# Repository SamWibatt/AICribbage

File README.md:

# MIGRATING FROM GITHUB TO GITLAB AT https://gitlab.com/SamWibatt/aicribbage - please go to that repository (unless you're already there.)

# AICribbage
Learned models for cribbage playing: discard, next card in count.

No learned players have yet been constructed - computer player is random / first legal pick.

# Status

As of (7/27/20), early. Python prototype (pybbage) that is the framework for learned players is complete and its correctness wrt American Cribbage Congress rules verified through unit testing. It has a text interface for playing it. 

**C++ development has been split off into [cribbage_cpp](https://github.com/SamWibatt/cribbage_cpp), where pybbage's functionality has been duplicated and verified through unit testing**.

# objective

* More self-teaching, this is like a "semester project" for showing I can use modern AI methods.
* Construct models for two player game, see if can transfer to others
* First concept is if I have models to:
    * decide which cards to discard from hand that's dealt
        * both as dealer and non-dealer
    * decide which card to play next in count
* will sketch design in wiki

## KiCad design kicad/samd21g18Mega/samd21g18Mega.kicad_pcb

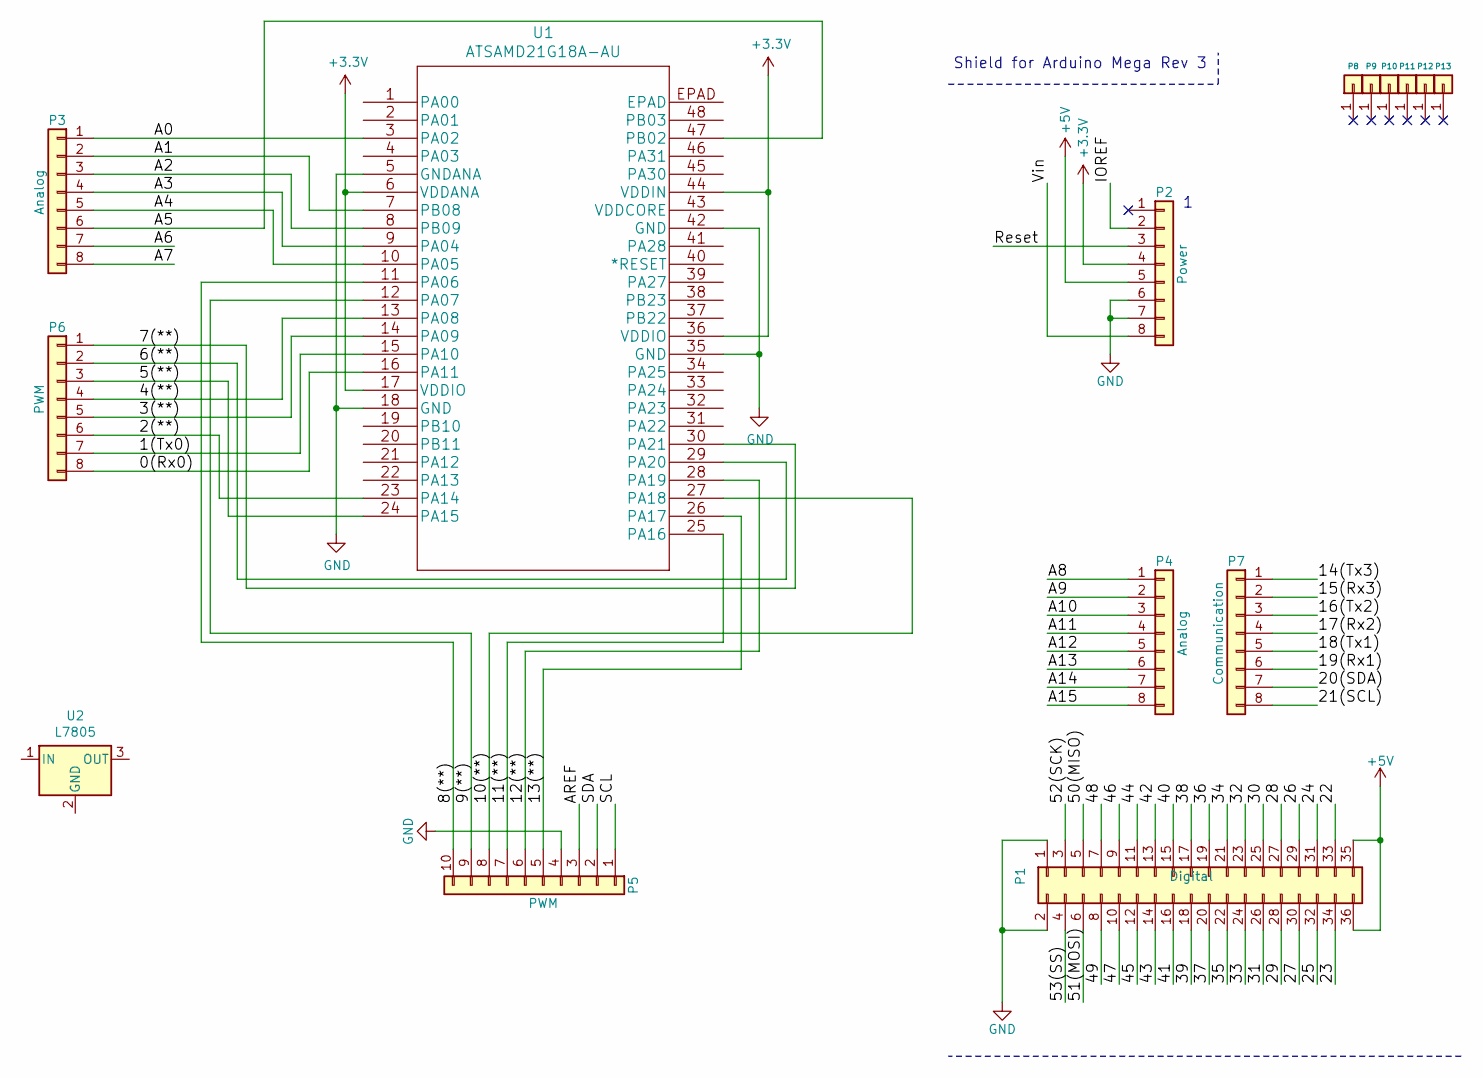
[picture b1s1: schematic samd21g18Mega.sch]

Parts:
P1: Digital; Socket_Strip_Arduino_2x18
P2: Power; Socket_Strip_Arduino_1x08
P3, P4: Analog; Socket_Strip_Arduino_1x08
P5: PWM; Socket_Strip_Arduino_1x10
P6: PWM; Socket_Strip_Arduino_1x08
P7: Communication; Socket_Strip_Arduino_1x08
P8, P9, P10, P11, P12, P13: CONN_01X01; Arduino_1pin
U1: ATSAMD21G18A-AU; DIP-48_W15.24mm
U2: L7805; TO-220-3_Horizontal_TabUp

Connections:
+3V3: P2.4, U1.6 (VDDANA), U1.17 (VDDIO), U1.36 (VDDIO), U1.44 (VDDIN)
+5V: P1.35, P1.36, P2.5
/0(Rx0): P6.8, U1.16 (PA11)
/1(Tx0): P6.7, U1.15 (PA10)
/2(**): P6.6, U1.23 (PA14)
/3(**): P6.5, U1.14 (PA09)
/4(**): P6.4, U1.13 (PA08)
/5(**): P6.3, U1.24 (PA15)
/6(**): P6.2, U1.29 (PA20)
/7(**): P6.1, U1.30 (PA21)
/8(**): P5.10, U1.11 (PA06)
/9(**): P5.9, U1.12 (PA07)
/10(**): P5.8, U1.27 (PA18)
/11(**): P5.7, U1.25 (PA16)
/12(**): P5.6, U1.28 (PA19)
/13(**): P5.5, U1.26 (PA17)
/14(Tx3): P7.1
/15(Rx3): P7.2
/16(Tx2): P7.3
/17(Rx2): P7.4
/18(Tx1): P7.5
/19(Rx1): P7.6
/20(SDA): P7.7
/21(SCL): P7.8
/22: P1.33
/23: P1.34
/24: P1.31
/25: P1.32
/26: P1.29
/27: P1.30
/28: P1.27
/29: P1.28
/30: P1.25
/31: P1.26
/32: P1.23
/33: P1.24
/34: P1.21
/35: P1.22
/36: P1.19
/37: P1.20
/38: P1.17
/39: P1.18
/40: P1.15
/41: P1.16
/42: P1.13
/43: P1.14
/44: P1.11
/45: P1.12
/46: P1.9
/47: P1.10
/48: P1.7
/49: P1.8
/50(MISO): P1.5
/51(MOSI): P1.6
/52(SCK): P1.3
/53(SS): P1.4
/A0: P3.1, U1.3 (PA02)
/A1: P3.2, U1.7 (PB08)
/A2: P3.3, U1.8 (PB09)
/A3: P3.4, U1.9 (PA04)
/A4: P3.5, U1.10 (PA05)
/A5: P3.6, U1.47 (PB02)
/A6: P3.7
/A7: P3.8
/A8: P4.1
/A9: P4.2
/A10: P4.3
/A11: P4.4
/A12: P4.5
/A13: P4.6
/A14: P4.7
/A15: P4.8
/AREF: P5.3
/IOREF: P2.2
/Reset: P2.3
/SCL: P5.1
/SDA: P5.2
/Vin: P2.8
GND: P1.1, P1.2, P2.6, P2.7, P5.4, U1.5 (GNDANA), U1.18 (GND), U1.35 (GND), U1.42 (GND)

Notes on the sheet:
Shield for Arduino Mega Rev 3

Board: 2 copper layers, 15 parts (0 on the bottom side), 23 nets, no tracks yet.

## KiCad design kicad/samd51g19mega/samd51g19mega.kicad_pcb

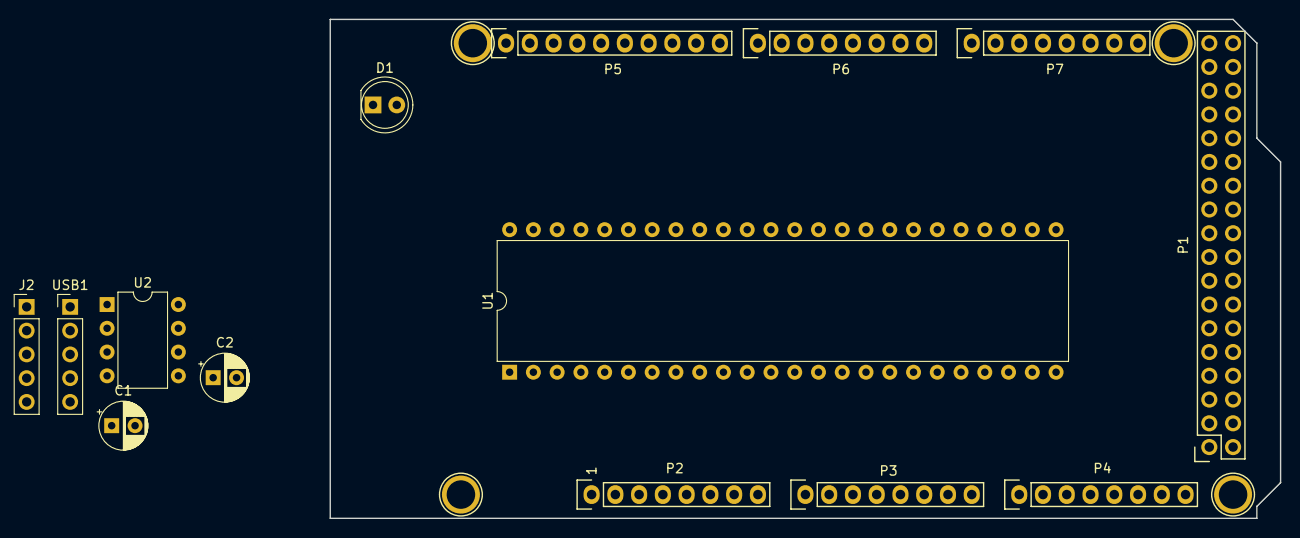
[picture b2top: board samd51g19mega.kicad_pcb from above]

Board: 2 copper layers, 101.6 x 53.3 mm, 18 parts (0 on the bottom side), 5 nets, no tracks yet.

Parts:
C1, C2: 10uF; CP_Radial_D5.0mm_P2.50mm
D1: LED; LED_D5.0mm
J2: Conn_01x05_Female; PinHeader_1x05_P2.54mm_Vertical
P1: Digital; Socket_Strip_Arduino_2x18
P2: Power; Socket_Strip_Arduino_1x08
P3, P4: Analog; Socket_Strip_Arduino_1x08
P5: PWM; Socket_Strip_Arduino_1x10
P6: PWM; Socket_Strip_Arduino_1x08
P7: Communication; Socket_Strip_Arduino_1x08
P8, P10, P11, P13: CONN_01X01; Arduino_1pin
U1: ATSAMD51G19A-MUT; DIP-48_W15.24mm
U2: W25Q64JVSSIQ; DIP-8_W7.62mm
USB1: USB_B_Micro; PinHeader_1x05_P2.54mm_Vertical

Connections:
+3V3: C2.1, P2.4
+5V: C1.1, J2.1, P1.35, P1.36, P2.5, USB1.1
GND: C1.2, C2.2, J2.5, P1.1, P1.2, P2.6, P2.7, P5.4, USB1.5
unnamed: J2.2, U1.33, USB1.2
unnamed: J2.3, U1.34, USB1.3

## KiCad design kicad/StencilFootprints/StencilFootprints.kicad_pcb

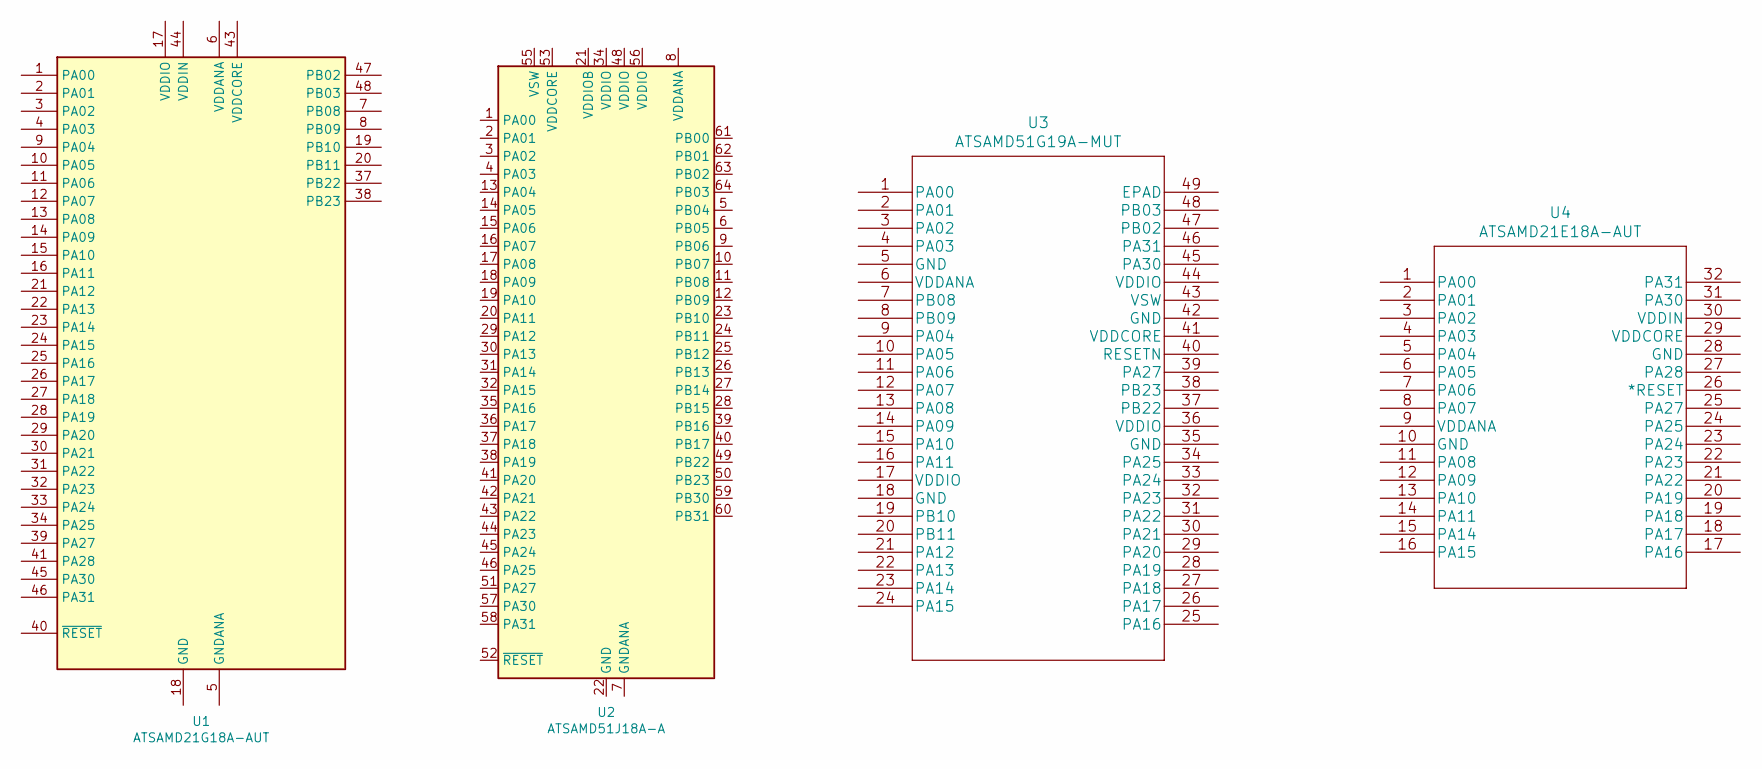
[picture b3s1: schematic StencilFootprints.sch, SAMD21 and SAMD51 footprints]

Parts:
U1: ATSAMD21G18A-AUT; TQFP-48_7x7mm_P0.5mm
U2: ATSAMD51J18A-A; TQFP-64_10x10mm_P0.5mm
U3: ATSAMD51G19A-MUT; QFN-48-1EP_7x7mm_P0.5mm_EP5.15x5.15mm
U4: ATSAMD21E18A-AUT; TQFP-32_7x7mm_P0.8mm

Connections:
unnamed: U1.17 (VDDIO), U1.36 (VDDIO)
unnamed: U1.18 (GND), U1.35 (GND), U1.42 (GND)
unnamed: U2.22 (GND), U2.33 (GND), U2.47 (GND), U2.54 (GND)

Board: 2 copper layers, 4 parts (0 on the bottom side), 3 nets, no tracks yet.

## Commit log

2020-03-08 set up pybbage project
2020-03-09 python prototype random
2020-03-12 shuffle and deal
2020-03-12 new shuffle and deal
2020-03-16 deal
2020-03-18 scoring 15s
2020-03-18 initial unit tests
2020-03-19 more scoring
2020-03-19 Missing case in test strcard legit
2020-03-19 further scoring work
2020-03-20 scoring maybe done
2020-03-20 dbl runs added
2020-03-20 initial show unit tests
2020-03-21 starting play-count
2020-03-21 preliminary play score
2020-03-22 play unit tests
2020-03-22 broken - started real gameplay
2020-03-22 verified random_at_most
2020-03-22 cut for deal
2020-03-22 up to first deal
2020-03-23 play partial
2020-03-23 comments re play
2020-03-24 play almost done
2020-03-24 getting close
2020-03-25 first mockup
2020-03-25 adding scores except go
2020-03-25 2nd mockup
2020-03-28 initial arduino commit and mockups
2020-03-29 improvements to convertpngtotft
2020-03-29 converter rotations
2020-03-29 play scoring apparently done
2020-03-29 fixed player order in play
2020-03-30 added debug of rotations to convertpngtotft
2020-03-30 dealer logic
2020-03-31 Game works maybe
2020-03-31 added score constants and strings
2020-03-31 score array fix
2020-04-01 shew score subsets refactor
2020-04-01 arcade requirement for graphic pybbage
2020-04-01 requirements.txt for grx pybbage
2020-04-01 initial checkin of graphics pybbage
2020-04-01 pybgrx bg image
2020-04-02 initial card deck reds only
2020-04-02 first test card deck
2020-04-02 card deck suits in order
2020-04-02 changed sprite to king horts
2020-04-02 khorts sprite and initial grx count layout
2020-04-02 added starter to pybgrx
2020-04-02 fixed starter bottom comment
2020-04-02 cribmock2serp
2020-04-03 card back and deck
2020-04-03 pegs in mockup
2020-04-04 initial hole positions
2020-04-05 highlight sprite
2020-04-05 highlights show
2020-04-05 highlight hiding and init starter cut mockup
2020-04-05 card cut mockup n highlights
2020-04-07 spi cribmock initial
2020-04-08 cribmock works
2020-04-08 stubbed mode class
2020-04-08 refactor to mode objects in progress (broken)
2020-04-09 further refactor
2020-04-09 mode refactor working
2020-04-09 mode class default methods
2020-04-10 title screen and mode change!
2020-04-10 initial pybbage class refactor
2020-04-10 refactored unit tests for pybbage
2020-04-10 pybbage object in grx, minor refactor
2020-04-11 pre-refactor sync
2020-04-11 refactored pybgrx into package
2020-04-11 score names image
2020-04-12 displaying a score name
2020-04-12 tick system roughed
2020-04-12 unfeathered score names and added number sprites
2020-04-12 incremental shew score placement
2020-04-13 callback test
2020-04-13 event list initial version
2020-04-13 added args to eventlist callbacks
2020-04-14 first working event list!
2020-04-14 score animation works but card deck sideways
2020-04-14 initial event list works fully
2020-04-14 improved shew timing
2020-04-16 count mockup n score anim time tweaks
2020-04-16 stubbed and mocked play mode
2020-04-17 more play mockup
2020-04-17 nother play mockup
2020-04-17 new play coords
2020-04-18 refactor so play() returns score indices
2020-04-19 few multiscore play unit tests
2020-04-19 peg advance callbacks
2020-04-21 added scores to play unit tests
2020-04-21 updated play unit tests for num cards
2020-04-22 stubbed player objects in pybgrx
2020-04-22 adding highlight sprites to playmode
2020-04-25 cards and highlights render in play
2020-04-26 Starter cut mode roughed
2020-04-29 added card highlight to starter cut
2020-05-01 cut starter initial interface
2020-05-05 Arduino mega project for samd21
2020-05-06 samd21 mega and whole deck cut grx
2020-05-06 cut for deal partly done
2020-05-07 cut for deal mode roughed
2020-05-11 sd21g18mega soldering guide, dealmode rough
2020-05-14 deal screen roughed, samd51 platform started
2020-05-14 GameMode mode hierarchy refactor
2020-05-21 rewrote pybbage shuffle
2020-05-22 changed so cards deal off the right end of the deck
2020-05-22 shuffle uses vpokrand but nothing else
2020-05-22 added new random_at_most
